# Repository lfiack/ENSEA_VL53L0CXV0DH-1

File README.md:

# ENSEA_VL53L0CXV0DH-1
Breakout board for VL53L0CXV0DH/1 TOF sensor

## Pinout

| num | pin   |
|:---:|:-----:|
| 1   | +3.3V |
| 2   | GND   |
| 3   | SCL   |
| 4   | SDA   |
| 5   | GPIO1 |
| 6   | XSHUT |

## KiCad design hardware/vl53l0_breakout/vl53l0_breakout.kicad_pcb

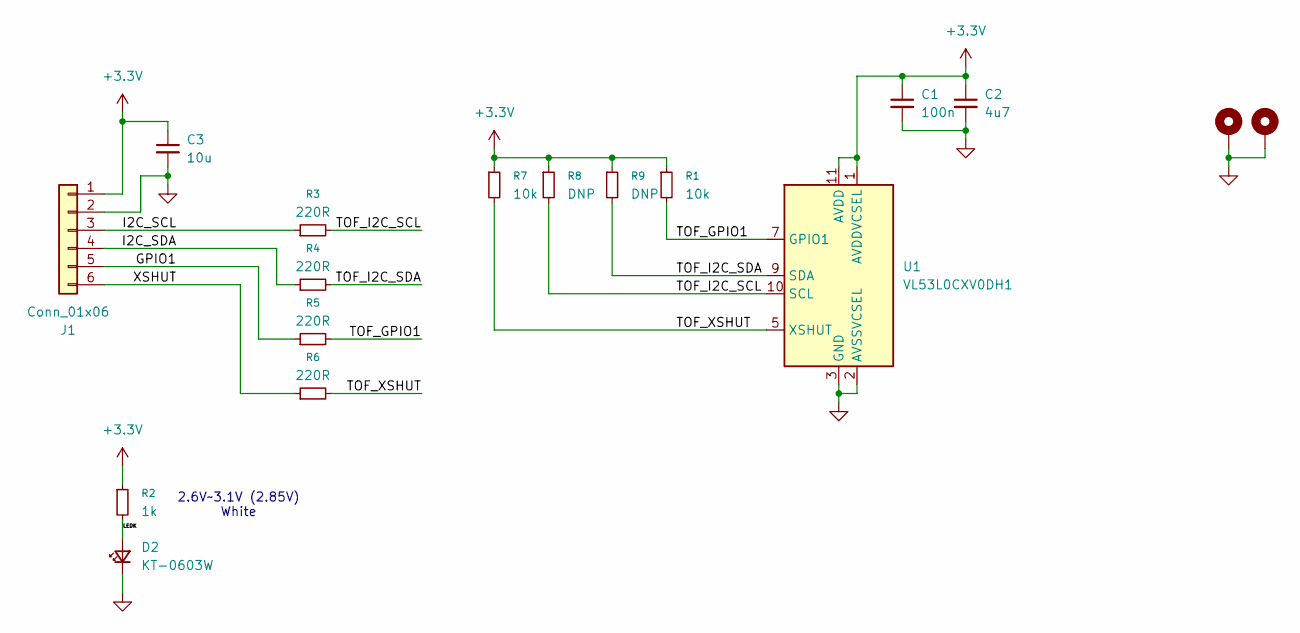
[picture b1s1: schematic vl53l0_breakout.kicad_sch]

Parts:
C1: 100n; C_0402_1005Metric; JLCPCB C1525
C2: 4u7; C_0402_1005Metric; JLCPCB C23733
C3: 10u; C_0603_1608Metric; JLCPCB C15850
D2: KT-0603W; LED_0603_1608Metric; JLCPCB C2290
H1, H2: MountingHole_Pad; MountingHole_2.2mm_M2_ISO7380_Pad
J1: Conn_01x06; PinHeader_1x06_P2.54mm_Vertical
R1, R7: 10k; R_0402_1005Metric; JLCPCB C25744
R2: 1k; R_0402_1005Metric; JLCPCB C11702
R3, R4, R5, R6: 220R; R_0402_1005Metric; JLCPCB C25091
R8, R9: DNP; C_0402_1005Metric_Pad0.74x0.62mm_HandSolder
U1: VL53L0CXV0DH1; ST_VL53L1x; JLCPCB C91199

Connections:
+3.3V: C1.1, C2.1, C3.1, J1.1, R1.1, R2.1, R7.1, R8.1, R9.1, U1.1 (AVDDVCSEL), U1.11 (AVDD)
/GPIO1: J1.5, R5.1
/I2C_SCL: J1.3, R3.1
/I2C_SDA: J1.4, R4.1
/LEDK: D2.2 (A), R2.2
/TOF_GPIO1: R1.2, R5.2, U1.7 (GPIO1)
/TOF_I2C_SCL: R3.2, R8.2, U1.10 (SCL)
/TOF_I2C_SDA: R4.2, R9.2, U1.9 (SDA)
/TOF_XSHUT: R6.2, R7.2, U1.5 (XSHUT)
/XSHUT: J1.6, R6.1
GND: C1.2, C2.2, C3.2, D2.1 (K), H1.1, H2.1, J1.2, U1.2 (AVSSVCSEL), U1.3 (GND), U1.4 (GND), U1.6 (GND), U1.12 (GND)

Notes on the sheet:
2.6V~3.1V (2.85V) White

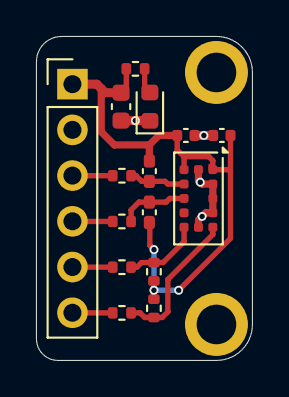
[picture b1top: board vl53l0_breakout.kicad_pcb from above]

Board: 2 copper layers, 12.0 x 18.0 mm, 17 parts (0 on the bottom side), 11 nets.

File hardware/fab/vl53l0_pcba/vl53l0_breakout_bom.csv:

Designator,Comment,Footprint,LCSC Part Number
C1,100n,402,C1525
C2,4u7,402,C23733
C3,10u,603,C15850
D2,KT-0603W,603,C2290
"R1,R7",10k,402,C25744
R2,1k,402,C11702
"R3,R4,R5,R6",220R,402,C25091
U1,VL53L0CXV0DH1,ST_VL53L0x,C91199

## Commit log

2025-09-16 schema
2025-09-16 routing
2025-09-17 modif + gerber
2025-09-17 fab files
2025-09-17 fab files organization
2025-09-17 final assembly files
